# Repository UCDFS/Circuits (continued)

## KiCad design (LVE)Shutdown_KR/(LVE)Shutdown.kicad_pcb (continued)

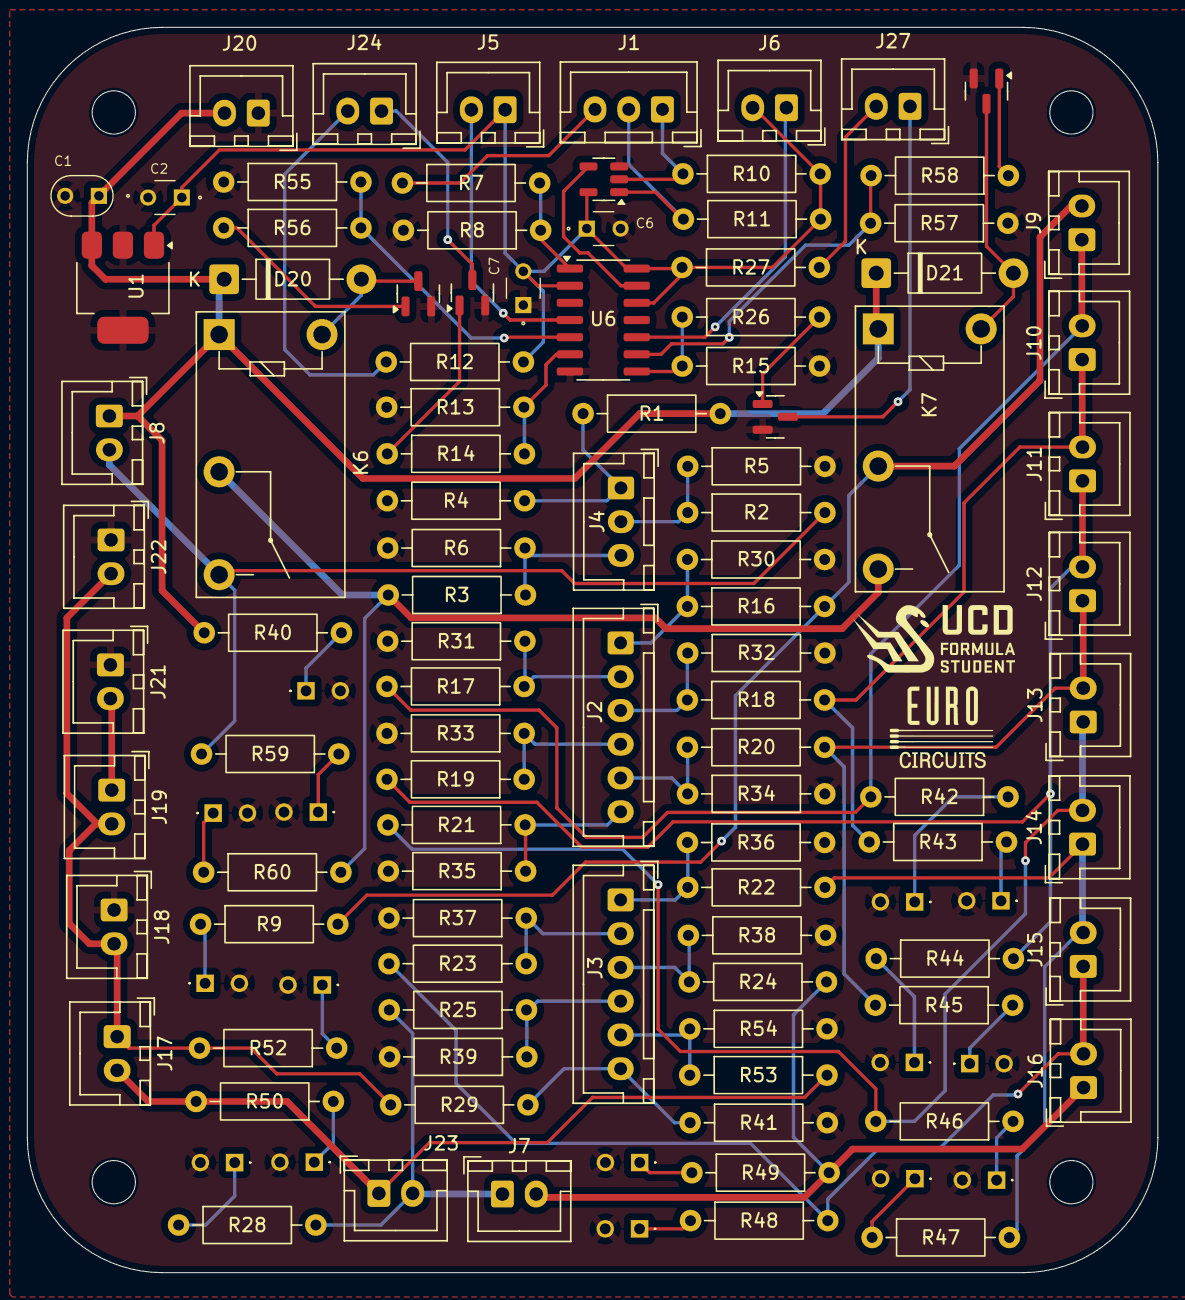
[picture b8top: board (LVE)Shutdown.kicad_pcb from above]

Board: 2 copper layers, 83.7 x 92.2 mm, 114 parts (0 on the bottom side), 69 nets.

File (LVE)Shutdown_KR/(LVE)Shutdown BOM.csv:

"Reference","Value","Part Number","Datasheet","Footprint","Qty","DNP"
"C1","0.22uF","FA14X7R1H224KNU00","http://www.farnell.com/datasheets/2923220.pdf","Kicad_Libraries:FA14X7R1H224KNU00","1",""
"C2,C6,C7","0.1uF","FA18X7R1H104KNU00","http://www.farnell.com/datasheets/2923220.pdf","Kicad_Libraries:FA18X7R1H104KNU00","3",""
"D20,D21","1N4001","1n4001","http://www.vishay.com/docs/88503/1n4001.pdf","Diode_THT:D_DO-41_SOD81_P10.16mm_Horizontal","2",""
"J1","Conn_01x03_Pin","B3B-XH-A","https://www.jst-mfg.com/product/pdf/eng/eXH.pdf","Connector_JST:JST_XH_B3B-XH-A_1x03_P2.50mm_Vertical","1",""
"J2,J3","Conn_01x06","B6B-XH-A","https://www.jst-mfg.com/product/pdf/eng/eXH.pdf","Connector_JST:JST_XH_B6B-XH-A_1x06_P2.50mm_Vertical","2",""
"J4","Conn_01x03","B3B-XH-A","https://www.jst-mfg.com/product/pdf/eng/eXH.pdf","Connector_JST:JST_XH_B3B-XH-A_1x03_P2.50mm_Vertical","1",""
"J5","IMD_RST","B2B-XH-A","https://www.jst-mfg.com/product/pdf/eng/eXH.pdf","Connector_JST:JST_XH_B2B-XH-A_1x02_P2.50mm_Vertical","1",""
"J6","AMS_RST","B2B-XH-A","https://www.jst-mfg.com/product/pdf/eng/eXH.pdf","Connector_JST:JST_XH_B2B-XH-A_1x02_P2.50mm_Vertical","1",""
"J7","HV_SENSE_INTL","B2B-XH-A","https://www.jst-mfg.com/product/pdf/eng/eXH.pdf","Connector_JST:JST_XH_B2B-XH-A_1x02_P2.50mm_Vertical","1",""
"J8","Conn_BSPD","B2B-XH-A","https://www.jst-mfg.com/product/pdf/eng/eXH.pdf","Connector_JST:JST_XH_B2B-XH-A_1x02_P2.50mm_Vertical","1",""
"J9","Conn_BTN_Cockpit","B2B-XH-A","https://www.jst-mfg.com/product/pdf/eng/eXH.pdf","Connector_JST:JST_XH_B2B-XH-A_1x02_P2.50mm_Vertical","1",""
"J10","Conn_BTN_Left","B2B-XH-A","https://www.jst-mfg.com/product/pdf/eng/eXH.pdf","Connector_JST:JST_XH_B2B-XH-A_1x02_P2.50mm_Vertical","1",""
"J11","Conn_BTN_Right","B2B-XH-A","https://www.jst-mfg.com/product/pdf/eng/eXH.pdf","Connector_JST:JST_XH_B2B-XH-A_1x02_P2.50mm_Vertical","1",""
"J12","Conn_BOTS_1","B2B-XH-A","https://www.jst-mfg.com/product/pdf/eng/eXH.pdf","Connector_JST:JST_XH_B2B-XH-A_1x02_P2.50mm_Vertical","1",""
"J13","Conn_BOTS_2","B2B-XH-A","https://www.jst-mfg.com/product/pdf/eng/eXH.pdf","Connector_JST:JST_XH_B2B-XH-A_1x02_P2.50mm_Vertical","1",""
"J14","Conn_Inertia","B2B-XH-A","https://www.jst-mfg.com/product/pdf/eng/eXH.pdf","Connector_JST:JST_XH_B2B-XH-A_1x02_P2.50mm_Vertical","1",""
"J15","Conn_HVD_INTL","B2B-XH-A","https://www.jst-mfg.com/product/pdf/eng/eXH.pdf","Connector_JST:JST_XH_B2B-XH-A_1x02_P2.50mm_Vertical","1",""
"J16","Conn_ACC_INTL","B2B-XH-A","https://www.jst-mfg.com/product/pdf/eng/eXH.pdf","Connector_JST:JST_XH_B2B-XH-A_1x02_P2.50mm_Vertical","1",""
"J17","Conn_TSMS","B2B-XH-A","https://www.jst-mfg.com/product/pdf/eng/eXH.pdf","Connector_JST:JST_XH_B2B-XH-A_1x02_P2.50mm_Vertical","1",""
"J18","Conn_discharge","B2B-XH-A","https://www.jst-mfg.com/product/pdf/eng/eXH.pdf","Connector_JST:JST_XH_B2B-XH-A_1x02_P2.50mm_Vertical","1",""
"J19","Conn_precharge","B2B-XH-A","https://www.jst-mfg.com/product/pdf/eng/eXH.pdf","Connector_JST:JST_XH_B2B-XH-A_1x02_P2.50mm_Vertical","1",""
"J20","Conn_Power","B2B-XH-A","https://www.jst-mfg.com/product/pdf/eng/eXH.pdf","Connector_JST:JST_XH_B2B-XH-A_1x02_P2.50mm_Vertical","1",""
"J21","Conn_AIR 1","B2B-XH-A","https://www.jst-mfg.com/product/pdf/eng/eXH.pdf","Connector_JST:JST_XH_B2B-XH-A_1x02_P2.50mm_Vertical","1",""
"J22","Conn_AIR 2","B2B-XH-A","https://www.jst-mfg.com/product/pdf/eng/eXH.pdf","Connector_JST:JST_XH_B2B-XH-A_1x02_P2.50mm_Vertical","1",""
"J23","Conn_TSAL_OK","B2B-XH-A","https://www.jst-mfg.com/product/pdf/eng/eXH.pdf","Connector_JST:JST_XH_B2B-XH-A_1x02_P2.50mm_Vertical","1",""
"J24","IMD_LED","B2B-XH-A","https://www.jst-mfg.com/product/pdf/eng/eXH.pdf","Connector_JST:JST_XH_B2B-XH-A_1x02_P2.50mm_Vertical","1",""
"J27","AMS_LED","B2B-XH-A","https://www.jst-mfg.com/product/pdf/eng/eXH.pdf","Connector_JST:JST_XH_B2B-XH-A_1x02_P2.50mm_Vertical","1",""
"K6,K7","G5Q1A4DC12","G5Q1A4DC12","https://www.omron.com/ecb/products/pdf/en-g5q.pdf","Relay_THT:Relay_SPST_Omron-G5Q-1A","2",""
"LED1,LED2,LED3,LED4,LED5,LED6,LED7,LED8,LED9,LED10,LED11,LED12,LED13,LED14,LED15","LTL-1CHG","LTL-1CHG","https://media.digikey.com/pdf/Data%20Sheets/Lite-On%20PDFs/L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","Kicad_Libraries:LTL1CHG","15",""
"Q1,Q2,Q3,Q5","2N7002","2N7002","https://www.onsemi.com/pub/Collateral/NDS7002A-D.PDF","Package_TO_SOT_SMD:SOT-23","4",""
"R1,R2,R3,R16,R17,R18,R19,R20,R21,R22,R23,R24,R25,R29,R53","27k","MCF 0.25W 27K","http://www.farnell.com/datasheets/3436052.pdf?_gl=1*1jbac1h*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","Resistor_THT:R_Axial_DIN0207_L6.3mm_D2.5mm_P10.16mm_Horizontal","15",""
"R4,R5,R6,R7,R8,R9,R10,R11,R13,R15,R28,R30,R31,R32,R33,R34,R35,R36,R37,R38,R39,R40,R41,R42,R43,R44,R45,R46,R47,R48,R49,R50,R52,R54,R55,R57,R59,R60","10k","MCF 0.25W 10K","https://www.farnell.com/datasheets/3436052.pdf?_gl=1*j4k0i6*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","Resistor_THT:R_Axial_DIN0207_L6.3mm_D2.5mm_P10.16mm_Horizontal","38",""
"R12,R14,R26,R27,R56,R58","100","MCF 0.25W 100","https://www.farnell.com/datasheets/3436052.pdf?_gl=1*j4k0i6*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","Resistor_THT:R_Axial_DIN0207_L6.3mm_D2.5mm_P10.16mm_Horizontal","6",""
"U1","LM7805MPX/NOPB","LM7805MPX/NOPB","https://www.ti.com/lit/gpn/lm7800","Package_TO_SOT_SMD:SOT-223-3_TabPin2","1",""
"U2","SN74AHC1G02DBVR","SN74AHC1G02DBVR","https://www.ti.com/lit/ds/symlink/sn74ahc1g02.pdf?ts=1738520903275","Package_TO_SOT_SMD:SOT-23-5","1",""
"U6","MC74HC74ADG","MC74HC74ADG","https://www.onsemi.com/download/data-sheet/pdf/mc74hc74a-d.pdf","Package_SO:SOIC-14_3.9x8.7mm_P1.27mm","1",""

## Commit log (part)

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2025-09-11 Ignore macOS .DS_Store files
2025-09-11 Add Teensy Breakout Board
2025-09-11 Add work in progress breakout board for new Teensy microcontroller
2025-09-11 Add Teensy 4.1 Breakout Board KiCad project
    Added new KiCad schematic, PCB, and project files for the Teensy 4.1 Breakout Board. Removed old submodules for the previous Teensy Breakout Board design.
2025-09-11 Initial plan
2025-09-11 Add comprehensive README.md for UCFS KiCad circuits repository
2025-09-11 Update organization name from UCFS to UCDFS throughout README
2025-09-11 Keelan Test
2025-09-11 ignore .lck file
2025-09-13 added existing circuits
2025-09-13 added global library
2025-09-13 removed local lib table
2026-01-22 breakout board v1 sizing
2026-01-22 breakout complete
2026-01-30 breakout updated and ENNOID BMS added
2026-02-02 precharge complete
2026-02-04 precharge and discharge fixed
2026-02-06 Voltage measurement completed
2026-02-06 added HVLV labels
2026-02-09 updated breakout
2026-02-12 ENNOID BMS PCBs completed
2026-02-15 slave pcb complete
2026-03-06 slave with new fuses added
2026-03-07 bms architecture notes made re charging and discharging
2026-03-10 copied teensy and apps schematic for esf screenshot
2026-04-21 Slave with SMD and no other fuses
2026-04-23 fused slave variant v1
2026-05-12 fuse boards
2026-05-21 master and slave updated
2026-05-24 new cells and updated slave
2026-05-24 added author
2026-05-26 ordered boards
